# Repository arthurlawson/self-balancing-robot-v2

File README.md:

# 🤖 Self-Balancing Robot V2

### A Drivable Self-Balancing Robot That Screams When It Falls!

An advanced self-balancing robot utilizing the **ESP32-S3 (N16R8)** computing core, driven by a custom **Kalman Filter** and high-frequency **PID control loop** system.

This project features a fully **custom-designed main controller PCB, proudly sponsored and manufactured by JLCPCB**.

Built entirely within the PlatformIO ecosystem, this hardware platform integrates an MPU6050 IMU, DRV8833 motor driver, 2S LiPo battery safety logic, lighting, and onboard speaker playback systems.

---

## Core Features

*   **Advanced Estimation:** Custom Kalman Filter implementation paired with an MPU6050 IMU for precise roll angle determination.
*   **Wireless Remote Control:** Directional steering control handled over a dedicated **ESP-NOW** wireless connection.
*   **Motion:** Dual-motor balancing algorithms with custom gain scheduling to aid in active control.
*   **Hardware Protection:** Automated motor shutdown constraints to prevent destructive runaway crashes.
*   **Power Management:** Active voltage checks safeguarding the 2S LiPo system from dropping beneath unsafe cell margins.
*   **Audio & Visuals:** Integrated 2P edison filament LED's with status animations alongside audio playback to make the robot scream.

---

## Quick Navigation Hub

To get started with assembling or programming the robot, navigate to the specific setup guides below:

*   **[Firmware Setup & Deployment](./firmware/SETUP_GUIDE.md):** Complete code overview, configuration walkthrough for `config.h`, custom audio formatting parameters, and PlatformIO flashing instructions.
*   **[Hardware Production & Assembly](./hardware/SETUP_GUIDE.md):** Access to print-ready `.3mf` files, raw SolidWorks CAD models, custom KiCad schematics, and factory-ready Gerber packages.
*   **[Bill of Materials (BOM)](./hardware/BOM.md):** The complete physical and electrical component checklist required to buy, print, and manufacture the robot.

---

## Project License

This repository is distributed under a custom **Non-Commercial Open-Source License**. 

*   **Personal & Educational Use:** Freely allowed to modify, merge, and run the code/hardware assets.
*   **Commercial Use:** Strictly prohibited from being sold, leased, or utilized for paid product development without explicit written consent from the copyright holder.

*See the full terms inside the accompanying [LICENSE](./LICENSE) file.*

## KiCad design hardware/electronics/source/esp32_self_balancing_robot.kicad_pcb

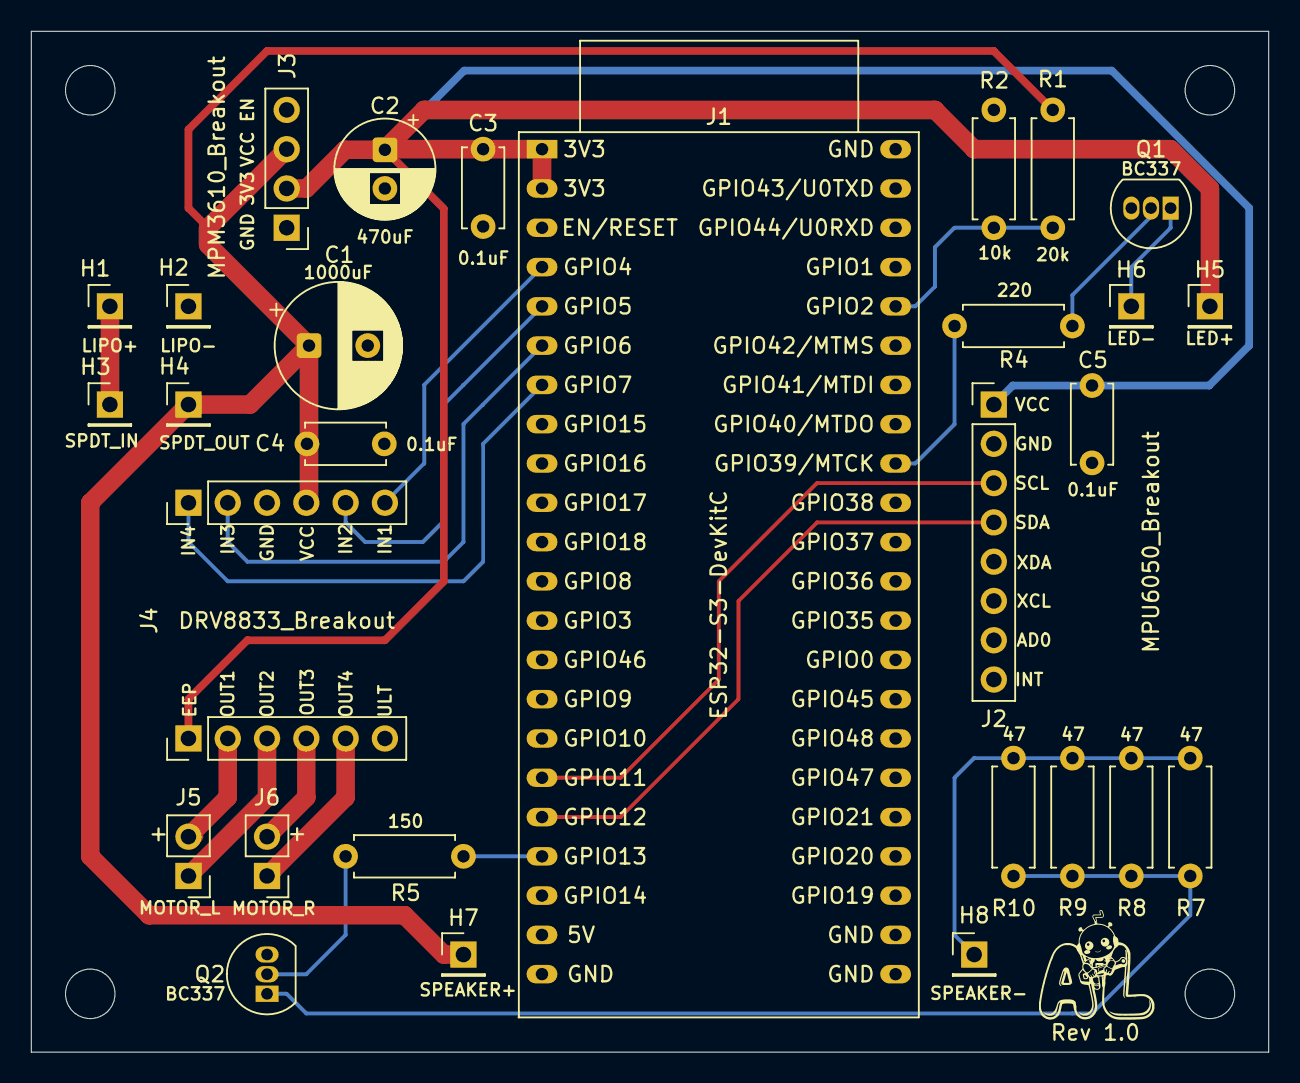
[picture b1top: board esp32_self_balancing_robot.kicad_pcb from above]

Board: 2 copper layers, 80.0 x 66.0 mm, 29 parts (0 on the bottom side), 18 nets.

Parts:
C1: 1000uF; CP_Radial_D8.0mm_P3.80mm
C2: 470uF; CP_Radial_D6.3mm_P2.50mm
C3, C4, C5: 0.1uf; C_Disc_D5.0mm_W2.5mm_P5.00mm
H1: LIPO+; PinHeader_1x01_P2.54mm_Vertical
H2: LIPO-; PinHeader_1x01_P2.54mm_Vertical
H3: SPDT_IN; PinHeader_1x01_P2.54mm_Vertical
H4: SPDT_OUT; PinHeader_1x01_P2.54mm_Vertical
H5: LED+; PinHeader_1x01_P2.54mm_Vertical
H6: LED-; PinHeader_1x01_P2.54mm_Vertical
H7: SPEAKER+; PinHeader_1x01_P2.54mm_Vertical
H8: SPEAKER-; PinHeader_1x01_P2.54mm_Vertical
J1: ESP32-S3-DevKitC
J2: MPU6050_Breakout; PinHeader_1x08_P2.54mm_Vertical
J3: MPM3610_Breakout; PinHeader_1x04_P2.54mm_Vertical
J4: DRV8833_Breakout; PinHeader_1x06_P2.54mm_Vertical
J5: LEFT_MOTOR; PinHeader_1x02_P2.54mm_Vertical
J6: RIGHT_MOTOR; PinHeader_1x02_P2.54mm_Vertical
Q1, Q2: BC337; TO-92_Inline
R1: 20k; R_Axial_DIN0207_L6.3mm_D2.5mm_P7.62mm_Horizontal
R2: 10k; R_Axial_DIN0207_L6.3mm_D2.5mm_P7.62mm_Horizontal
R4, R5: 220; R_Axial_DIN0207_L6.3mm_D2.5mm_P7.62mm_Horizontal
R7, R8, R9, R10: 47; R_Axial_DIN0207_L6.3mm_D2.5mm_P7.62mm_Horizontal

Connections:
+3.3V: C2.1, C3.2, C5.1, H5.1 (1_1), J1.1 (3V3), J1.2 (3V3), J2.1 (VCC), J3.2 (3V3), J4.1 (EEP)
/BATT_SENSE_PIN: J1.40 (GPIO2/ADC1_CH1), R1.1, R2.1
/LED_PIN: J1.36 (GPIO39/MTCK), R4.2
/SCL_PIN: J1.17 (GPIO11/ADC2_CH0), J2.3 (SCL)
/SDA_PIN: J1.18 (GPIO12/ADC2_CH1), J2.4 (SDA)
/SPEAKER_PIN: J1.19 (GPIO13/ADC2_CH2), R5.2
/VBAT: C1.1, C4.2, H4.1 (1_1), H7.1 (1_1), J3.3 (VIN), R1.2
GND: C1.2, C2.2, C3.1, C4.1, C5.2, H2.1 (1_1), J1.22 (GND), J1.23 (GND), J1.24 (GND), J1.44 (GND), J2.2 (GND), J3.1 (GND), Q1.3 (E), Q2.3 (E), R2.2
unnamed: H1.1 (1_1), H3.1 (1_1)
unnamed: H8.1 (1_1), R7.1, R8.1, R9.1, R10.1
unnamed: J4.2 (OUT1), J5.2
unnamed: J4.3 (OUT2), J5.1
unnamed: J4.4 (OUT3), J6.2
unnamed: J4.5 (OUT4), J6.1
unnamed: Q1.2 (B), R4.1
unnamed: H6.1 (1_1), Q1.1 (C)
unnamed: Q2.2 (B), R5.1
unnamed: Q2.1 (C), R7.2, R8.2, R9.2, R10.2

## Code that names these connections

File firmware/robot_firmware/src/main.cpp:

/**
 * @file main.cpp
 * @brief Entry point for the Self Balancing Robot
 * 
 * @author Arthur Lawson
 */

#include <config.h>
#include "utils/kalman_filter/kalman_filter.h"
#include "utils/pid_controller/pid_controller.h"
#include "drivers/motor_driver/drv8833.h"
#include "drivers/audio_driver/audio_driver.h"
#include "services/imu_service/imu_service.h"
#include "services/led_service/led_service.h"
#include "services/power_service/power_service.h"
#include "services/remote_service/remote_service.h"
#include "system/robot_controller/robot_controller.h"

// UTILS
KalmanFilter kf;
PidController pid;

// DRIVERS
DRV8833 motors(IN1_PIN, IN2_PIN, IN3_PIN, IN4_PIN);
AudioDriver speaker(SPEAKER_PIN);

// SERVICES
ImuService imuSvc(kf);
LedService ledSvc(LED_PIN);
PowerService pwrSvc(BATT_PIN, ledSvc);
RemoteService remote;

// ROBOT CONTROL SYSTEMS
RobotController robot(imuSvc, ledSvc, pwrSvc, motors, pid, kf, speaker);

// HARDWARE TIMER
volatile bool timerFlag = false;
hw_timer_t *timer = NULL;

void ARDUINO_ISR_ATTR onTimer() {
  timerFlag = true;
}

void setup() {
  Serial.begin(115200);
  delay(200);

  Serial.println("\n[BOOT] Power rails stabilized. Initiating hardware mounts...");

  randomSeed(analogRead(0));

  // 2. Safely initialize your speaker driver to clamp your transistor gate
  if (!speaker.Begin()) {
    Serial.println("[BOOT] WARNING: Audio Driver mount failed to clear filesystem.");
  }

  if (!imuSvc.Begin(SDA_PIN, SCL_PIN)) {
    while (1) {
      Serial.println("IMU Initialization Failed.");
      delay(1000);
    }
  }

  ledSvc.Begin();
  pwrSvc.Begin();
  remote.Begin(robot);

  robot.Begin();

  timer = timerBegin(0, TIMER_PRESCALER, true);
  timerAttachInterrupt(timer, &onTimer, true);
  timerAlarmWrite(timer, TIMER_ALARM_US, true);
  timerAlarmEnable(timer);

  Serial.println("System Core Ready!");
}

void loop() {
  if (timerFlag) {
    timerFlag = false;

    ledSvc.Update();
    imuSvc.Update();
    remote.Update();
    robot.Update();
  }
}
